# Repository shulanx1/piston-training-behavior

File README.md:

# README #

* Behavioral training set up for two whisker discrimination task based on pneumetic whisker stimulation

### Python environment Requirement: ###
* numpy
* scipy
* playsound
* pyserial

### Hardware on the circuit board: ###
* 24 V piston air pressure regulator: https://www.smcpneumatics.com/V114T-5LZ-M5.html
* 24 VDC power relay: digikey 255-5324-5-ND
* dual channel diod: digikey 1655-BAT54CCT-ND
* dual channel NTN transister: digikey MBT3904DW1T1G
* 12 V water valve: Nresearch 161K011 or thevalveshop 411L3112HV https://www.thevalveshop.com/menu/auto/asco/asco-scientific.html 
* 12 V water valve driver: Nresearch 161D1X250
* 5V speaker (with amplifier): digikey 1528-1746-ND
* vibration motor: 3V
* stepper motor: Makeblock Me Stepper Motor Driver https://amicus.com.sg/shop/makeblock/me-stepper-motor-driver/
* rotary encoder: https://www.usdigital.com/products/encoders/incremental/rotary/shaft/H5
* piezo based lickometer:<br />
single-rail op-amp: TLV2771CDBVR<br />
shunt regulator: ATL431BQDBZR<br />
non-inverting svhmitt trigger: SN74LVC1G17DBVR<br />
LED: 160-1183-1-ND<br />
trimmer resistor: digikey 3362P-504LF-ND<br />
* piezo based lickometer (with rail splitter:<br />
op-amp: TLV2371IDBVR<br />
rail splitter: TLE2426QDRG4Q1 <br />
cap 200nF: 1189-2375-ND  <br />
cap 1uF: 399-ESS105M050AB2EACT-ND <br\>

### pin layout V6 ###
* D2: capacitance/piezo lick sensor
* D3: water valve
* D5, D6: rotary encoder (A,B)
* D8, D9, D11, D12: piston
* D10: sliding switch (start trigger)
* A1, A2: LED/conductance lick sensor
* A3: speaker
* D11, D7: stepper motor (STP, DIR)
* D4, D12: vibrating piezo

### pin layout V7 ###
* D2: capacitance/piezo lick sensor
* D3: water valve
* D4: sliding switch (start trigger)
* D5, D6, A2: rotary encoder (A,B,rotations)
* D8, D9, A4, A5: piston
* A1: LED/conductance lick sensor
* A3: speaker
* A5, A4: stepper motor (STP, DIR)

### Files ###

* //BehavioralPCB: arduino code to upload to arduino uno (board V6)
* //Bonsai lick detection: real time lick detection with webcam when capactive based lick sensor causes electrical artifact
* //training.py: training file to serial communicate with arduino
* //behavior_training_decode: matlab file to decode the serial output of arduino
* //Arduino_board_V6: PCB design
* //CAD: laser engraving pattern on the running disk

### Install ###
* Arduino: <br />
At sketch -> include library -> add .zip library, add the dio2.zip folder<br />

* Python: <br />
on the command window, run: <br />
-- pip install playsound <br />
-- pip install pyserial <br />

### To start the training from command window ###
-- cd path-to-base-folder <br />
-- python training.py COM12 ear-tag-number phase <br />

### Training phase ###
* 1: no whisker stim, reward dispense when the lick is detected
* 2: GO and NOGO stim, with teaching signal
* 3: GO and NOGO stim, reward is given at "hit", time out at false alarm
* 4: optogenetic stimulation in randomly chosen half of the trials,  reward is given at "hit", time  out at false alarm

### Arduino test serial command ###
* 'v': test valve
* 'p': test pistons
* 'c': test cue sound
* 'f': flush the valve
* 'g': GO piston, use the sliding switch to turn on and off
* 'n': NOGO piston, use the sliding switch to turn on and off

### Arduino serial output row ###
* 1: rotary decoder
* 2: licking
* 3: valve
* 4: GO piston
* 5: NOGO piston
* 6: hit rate
* 7: false alarm rate
* 8: time

### Arduino pin map ###
* DO2: lick sensor
* DO3: valve
* DO5&DO6: rotary encoder
* D8, D9, D12, D12: pistons
* D10: sliding switch
* D13: trigger

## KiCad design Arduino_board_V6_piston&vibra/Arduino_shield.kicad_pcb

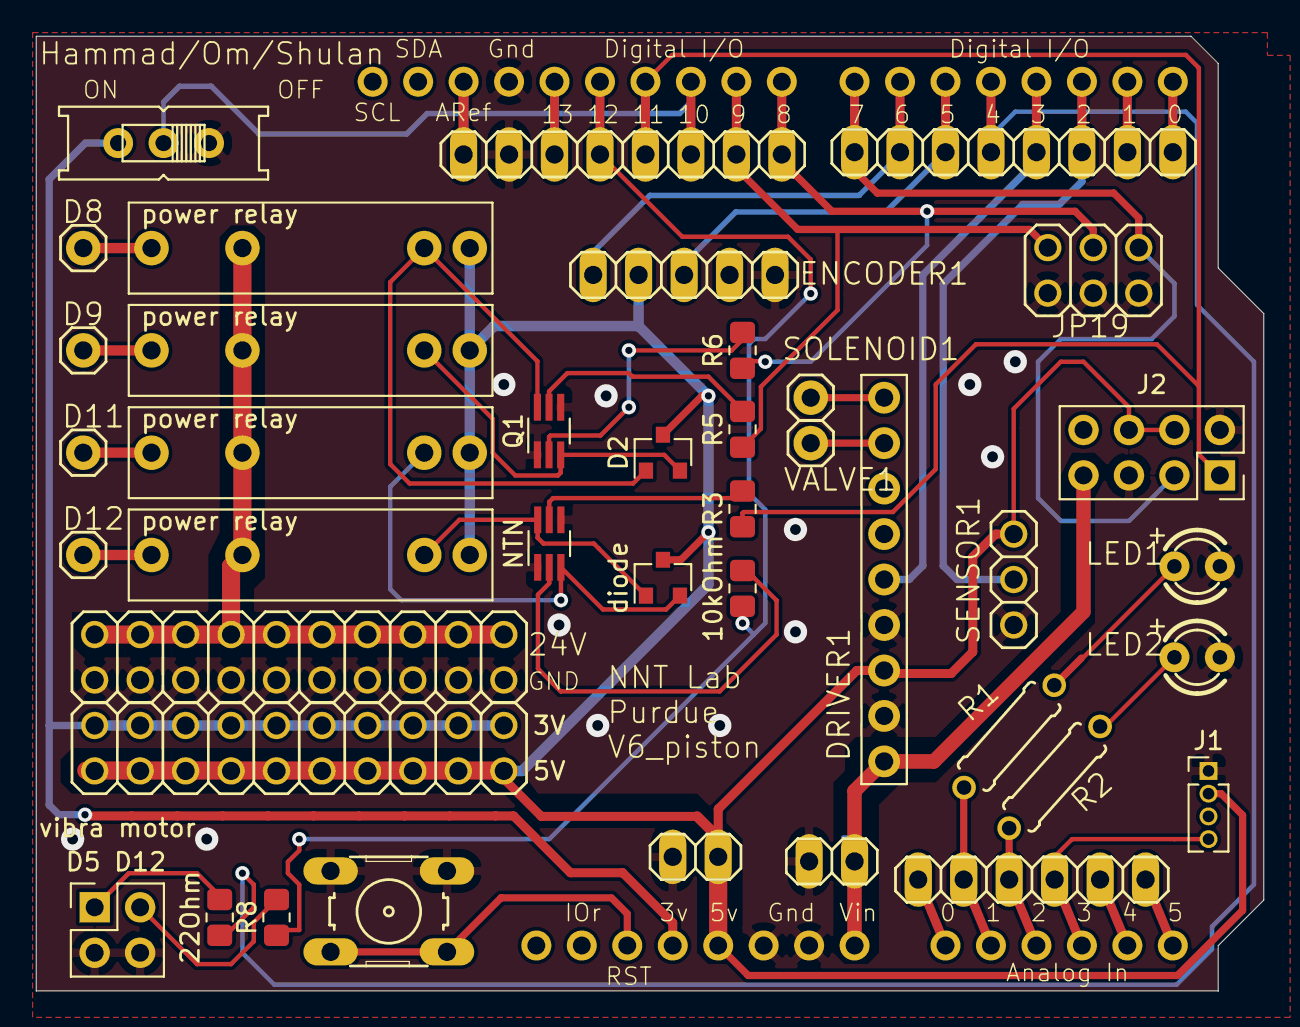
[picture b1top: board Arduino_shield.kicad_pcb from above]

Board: 2 copper layers, 68.6 x 53.3 mm, 41 parts (0 on the bottom side), 45 nets.

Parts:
10kOhm, 22Ohm: R; R_0805_2012Metric_Pad1.20x1.40mm_HandSolder
D2: BAT54C; SOT-23
D8, D9, D11, D12: Conn_01x01_Male; 1X01
DRIVER1: PINHD-1X9; 1X09-BIG
ENCODER1: PINHD-1X5; 1X05
J1: Conn_01x04_Male; PinHeader_1x04_P1.27mm_Vertical
J2: Conn_02x04_Odd_Even; PinSocket_2x04_P2.54mm_Vertical
JP7, JP8: PINHD-1X8; 1X08
JP9, JP10: PINHD-1X2; 1X02
JP11: PINHD-1X6; 1X06
JP16, JP17: PINHD-2X10; 2X10
JP19: PINHD-2X3; 2X03
LED1, LED2: LED3MM
NTN: Q_DUAL_NPN_NPN_BRT_E1B1C2E2B2C1; SOT-363_SC-70-6_Handsoldering
Q1: Q_DUAL_NPN_NPN_BRT_E1B1C2E2B2C1; SOT-363_SC-70-6_Handsoldering
R1, R2: R-EU_0207_7; 0207_7
R3, R5, R6, R8: R; R_0805_2012Metric_Pad1.20x1.40mm_HandSolder
S1: EG1218S; EG1218
S2: 10-XX; B3F-10XX
SENSOR1: PINHD-1X3; 1X03
SOLENOID1: PINHD-1X1; 1X01
U1: ARDUINOR3-DIMENSION; ARDUINOR3
VALVE1: PINHD-1X1; 1X01
diode: BAT54C; SOT-23
power relay: Conn_01x04_Male; power_relay_PA-N
power relay#2, power relay#3, power relay#4: Conn_01x04_Male; power_relay_PA-N
vibra motor: Conn_02x02_Odd_Even; PinHeader_2x02_P2.54mm_Vertical

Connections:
3V: JP16.2, JP16.4, JP16.6, JP16.8, JP16.10, JP16.12, JP16.14, JP16.16, JP16.18, JP16.20, S1.S, U1.3V
12V: DRIVER1.1, J2.7, JP10.1, U1.VIN
/A: ENCODER1.3, JP7.6, U1.D5
/A0: JP11.1, U1.A0
/A1: JP11.2, R1.2, U1.A1
/A2: JP11.3, R2.2, U1.A2
/A3: J1.4, JP11.4, U1.A3
/A4: JP11.5, U1.A4
/A5: JP11.6, U1.A5
/AREF: JP8.8, U1.AREF
/B: ENCODER1.5, JP7.7, U1.D6
/D0: JP7.1, U1.D0
/D1: JP7.2, U1.D1
/D2: JP7.3, SENSOR1.2, U1.D2
/D3: DRIVER1.5, JP7.4, U1.D3
/RECORD: JP8.3, S1.P, U1.D10
/RESET: S2.3, S2.4, U1.RESET
/SCK: JP8.6, U1.D13
CS: 22Ohm.1, JP7.5, U1.D4
D7: J2.3, JP7.8, JP19.6, U1.D7
D8: JP8.1, JP19.4, R6.1, U1.D8
D9: JP8.2, JP19.2, R5.1, U1.D9
GND: DRIVER1.2, DRIVER1.4, ENCODER1.1, J1.1, J2.2, J2.5, JP8.7, JP9.2, JP10.2, JP17.1, JP17.3, JP17.5, JP17.7, JP17.9, JP17.11, JP17.13, JP17.15, JP17.17, JP17.19, JP19.1, JP19.3, JP19.5, LED1.K, LED2.K, NTN.1, NTN.4, Q1.1, Q1.4, S1.O, S2.1, S2.2, SENSOR1.3, U1.GND, U1.GND1, U1.GND2, vibra motor.3, vibra motor.4
MISO: 10kOhm.1, JP8.5, R8.1, U1.D12
MOSI: J2.1, JP8.4, R3.1, U1.D11
unnamed: NTN.6, diode.1, power relay#3.2
unnamed: NTN.3, diode.2, power relay#2.2
unnamed: D2.1, Q1.6, power relay.2
unnamed: D2.2, Q1.3, power relay#4.2
unnamed: DRIVER1.8, VALVE1.1
unnamed: DRIVER1.9, SOLENOID1.1
unnamed: D9.1, power relay#4.4
unnamed: D8.1, power relay.4
unnamed: D11.1, power relay#2.4
unnamed: D12.1, power relay#3.4
unnamed: 22Ohm.2, vibra motor.1
unnamed: R8.2, vibra motor.2
unnamed: LED1.A, R1.1
unnamed: LED2.A, R2.1
unnamed: Q1.2, R6.2
unnamed: Q1.5, R5.2
unnamed: 10kOhm.2, NTN.2
unnamed: NTN.5, R3.2
VCC: D2.3, DRIVER1.3, ENCODER1.4, J1.2, J2.4, J2.6, JP9.1, JP16.1, JP16.3, JP16.5, JP16.7, JP16.9, JP16.11, JP16.13, JP16.15, JP16.17, JP16.19, SENSOR1.1, U1.5V, diode.3, power relay.1, power relay#2.1, power relay#3.1, power relay#4.1
VDD_24V: JP17.2, JP17.4, JP17.6, JP17.8, JP17.10, JP17.12, JP17.14, JP17.16, JP17.18, JP17.20, power relay.3, power relay#2.3, power relay#3.3, power relay#4.3

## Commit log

2023-01-28 origin
2023-04-24 updated with teaching signal in training
2023-04-24 Initial Bitbucket Pipelines configuration
2023-04-24 bitbucket-pipelines.yml edited online with Bitbucket
2023-07-04 change the arduino output
2023-07-07 piezo licometer added
2023-07-14 minor changes
2024-07-17 added V7 board with SD card slot
